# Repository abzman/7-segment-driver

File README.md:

7-segment-driver
================

TTL level driver for 7-segment display
This uses a BCD to 7-segment driver and an up/down counter IC with buttons.  It really needs debouncing on the buttons and the board is a very primitive layout

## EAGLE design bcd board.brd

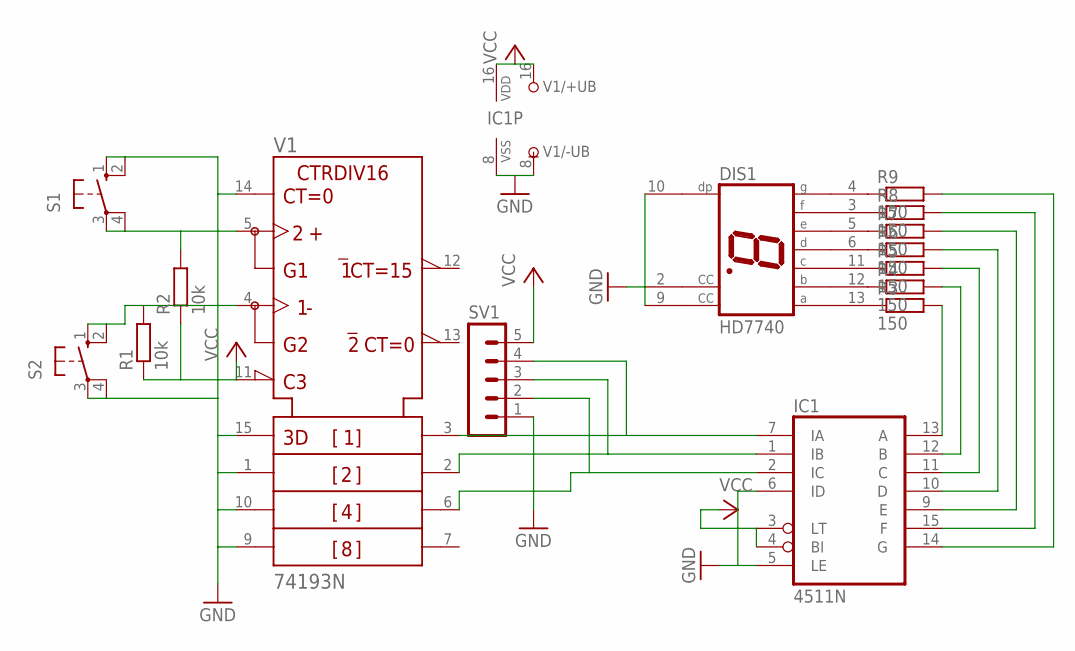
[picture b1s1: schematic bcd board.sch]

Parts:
DIS1: HD7740; HD7730
IC1: 4511N; DIL16
R1, R2: 10k; 0204/7
R3, R4, R5, R6, R7, R8, R9: 150; 0204/7
S1, S2: 10-XX; B3F-10XX
SV1: MA05-1
V1: 74193N; DIL16

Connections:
GND: DIS1.2 (CC), DIS1.9 (CC), DIS1.10 (DP), IC1.5 (LE), IC1.6 (ID), IC1.8 (VSS), S1.1 (S), S1.2 (S1), S2.3, S2.4 (P1), SV1.1, V1.1 (B), V1.8 (-UB), V1.9 (D), V1.10 (C), V1.14 (CLR), V1.15 (A)
unnamed: DIS1.13 (A), R3.1
unnamed: DIS1.12 (B), R4.1
unnamed: DIS1.11 (C), R5.1
unnamed: DIS1.6 (D), R6.1
unnamed: DIS1.5 (E), R7.1
unnamed: DIS1.3 (F), R8.1
unnamed: DIS1.4 (G), R9.1
unnamed: IC1.13 (A), R3.2
unnamed: IC1.12 (B), R4.2
unnamed: IC1.11 (C), R5.2
unnamed: IC1.10 (D), R6.2
unnamed: IC1.9 (E), R7.2
unnamed: IC1.15 (F), R8.2
unnamed: IC1.14 (G), R9.2
unnamed: R2.2, S1.3, S1.4 (P1), V1.5 (UP)
unnamed: IC1.1 (IB), SV1.3, V1.2 (QB)
unnamed: R1.2, S2.1 (S), S2.2 (S1), V1.4 (DOWN)
unnamed: IC1.7 (IA), SV1.4, V1.3 (QA)
unnamed: IC1.2 (IC), SV1.2, V1.6 (QC)
VCC: IC1.3 (LT), IC1.4 (BI), IC1.16 (VDD), R1.1, R2.1, SV1.5, V1.11 (!LOAD), V1.16 (+UB)

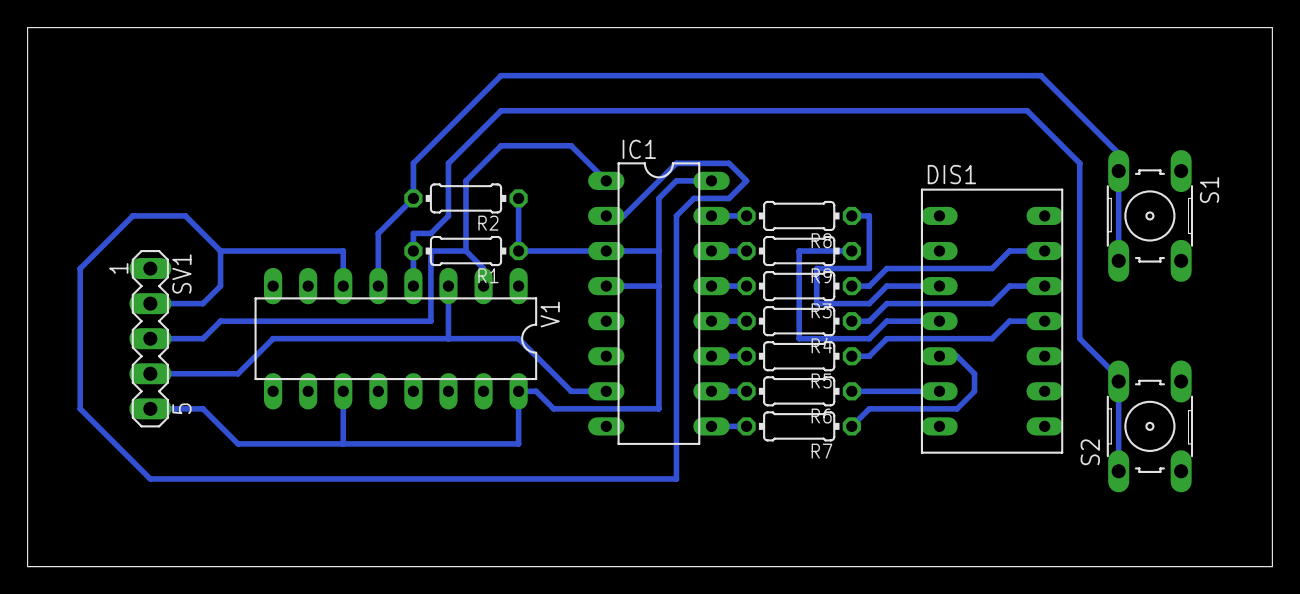
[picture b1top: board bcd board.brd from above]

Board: 2 copper layers, 90.1 x 39.0 mm, 15 parts (0 on the bottom side), 21 nets.
